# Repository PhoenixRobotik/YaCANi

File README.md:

# YaCANi: Yet another CAN interface

The YaCANi is forked from the [CANtact project](https://github.com/CANtact/cantact-hw).  
The goal was a smaller PCB with micro USB and a specific CAN connector (JST XH). Some components have also been replaced by components we use on our other projects.

It have been designed with [KiCad](http://www.kicad-pcb.org/).

You might be interested in others forks of [CANtact project](https://github.com/CANtact/cantact-hw):
- [Canable](http://canable.io/): smaller PCB than CANtact, designed on Eagle CAD (we took a lot of inspiration from it)
- [x893's fork](https://github.com/x893/cantact-hw): uses ADM3053 CAN transceiver (for it's isolation capability)

## License

Hardware files released under the [Creative Commons Attribution-ShareAlike 4.0
International License](http://creativecommons.org/licenses/by-sa/4.0/) 
(CC BY-SA 4.0)

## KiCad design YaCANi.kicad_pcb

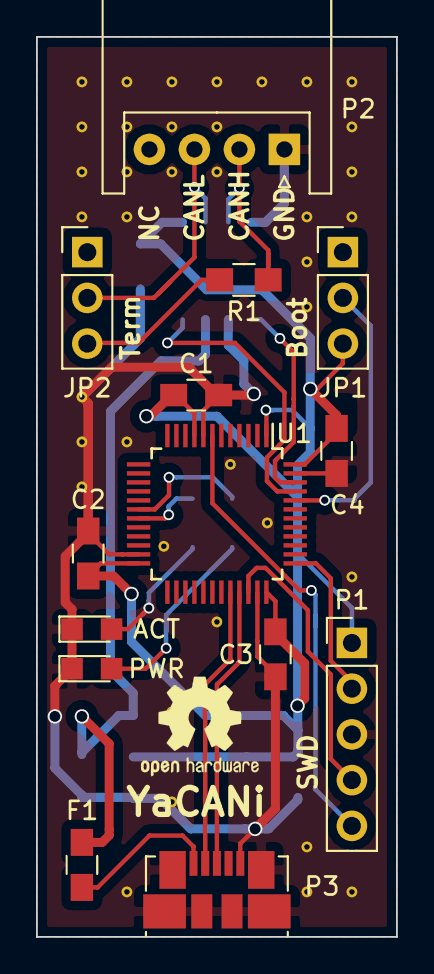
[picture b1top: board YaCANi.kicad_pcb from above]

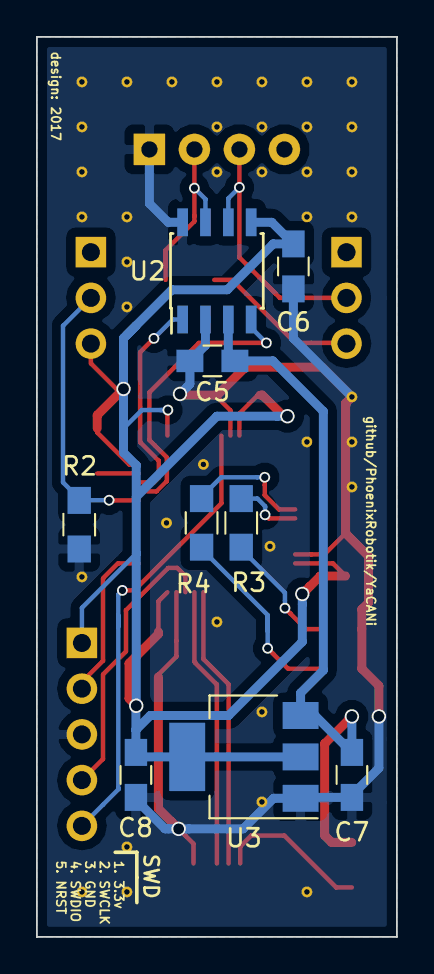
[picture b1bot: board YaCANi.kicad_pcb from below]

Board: 2 copper layers, 20.0 x 50.0 mm, 23 parts (9 on the bottom side), 19 nets.

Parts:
ACT: LED-RED; LED_0805
C1, C2, C4, C5, C6: 0.1uF; C_0805_HandSoldering
C3: 1uF; C_0805_HandSoldering
C7: 100nF; C_0805_HandSoldering
C8: 10uF; C_0805_HandSoldering
F1: Polyfuse; C_0805_HandSoldering
JP1, JP2: Jumper_NC_Dual; Pin_Header_Straight_1x03_Pitch2.54mm
P1: SWD; Pin_Header_Straight_1x05_Pitch2.54mm
P2: CAN; JST_XH_S04B-XH-A_04x2.50mm_Angled
P3: USB; USB_Micro-B_Molex_47346-0001
PWR: LED-GREEN; LED_0805
R1: 120; R_0805_HandSoldering
R2: 10k; R_0805_HandSoldering
R3, R4: R; R_0805_HandSoldering
U1: STM32F042C6T6; LQFP-48_7x7mm_Pitch0.5mm
U2: MCP2562-E/SN; SOIC-8_3.9x4.9mm_Pitch1.27mm
U3: LD1117S33TR; SOT-223

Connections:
+3V3: C1.1, C2.1, C3.1, C4.1, C6.2, C8.1, JP1.3, P1.1, U1.1, U1.9, U1.24, U1.36, U1.48, U2.5, U3.2
+5V: C5.2, C7.1, F1.2, U2.3, U3.3
/CAN_RX: U1.45, U2.4
/CAN_TX: U1.46, U2.1
/NRST: P1.5, U1.7
/SWCLK: P1.2, U1.37
/SWDIO: P1.4, U1.34
/USB_DM: P3.2, U1.32
/USB_DP: P3.3, U1.33
BOOT0: JP1.2, R2.1, U1.44
CAN_H: P2.2, R1.2, U2.7
CAN_L: JP2.2, P2.3, U2.6
GND: ACT.1, C1.2, C2.2, C3.2, C4.2, C5.1, C6.1, C7.2, C8.2, P1.3, P2.1, P3.5, P3.6, PWR.1, R2.2, U1.8, U1.23, U1.35, U1.47, U2.2, U2.8, U3.1
LED_ACT: R3.2, U1.19
LED_PWR: R4.2, U1.18
unnamed: ACT.2, R3.1
unnamed: PWR.2, R4.1
unnamed: F1.1, P3.1
unnamed: JP2.3, R1.1

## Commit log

2017-03-20 remove gerbers
2017-03-20 change gitignore
2017-03-20 remove pretty libs
2017-03-20 remove BOM
2017-03-20 remove .net file
2017-03-20 rename files
2017-03-20 updated libs, footprints
2017-03-20 Edit Readme
2017-03-20 correct USB connector
2017-03-20 add infos on README.md
2017-03-23 change MCP2561 for MCP2562
2017-03-23 add USB 5v fuse
2017-03-23 presentation
2017-03-23 replace DB9 connector with JST-XH and add 120ohm resistor jumper
2017-03-23 add boot jumper
2017-03-23 remove 16MHz crystal
2017-03-23 change regulator
2017-03-23 move LED and change logic
2017-03-23 add some text on schematic
2017-03-23 change LED labels
2017-03-23 remove some decoupling capacitors (ouch !) + numbering
2017-03-23 just some formating
2017-03-23 new footprints on pcb
2017-03-24 correct missing connection
2017-03-24 correct wrong connection
2017-03-24 first placement and quick routing
2017-03-24 just change a via
2017-03-24 remove test points
2017-03-24 proper track size
2017-03-24 DRC ok
2017-03-24 first version ?
2017-03-24 remove useless via
2017-03-24 change CAN connector to an angled version
2017-03-24 move CAN connector
2017-03-24 add text on board
2017-03-24 add logo and referencies
2017-03-24 add LED labelling
2017-03-24 add design date
2017-04-23 add TODO
